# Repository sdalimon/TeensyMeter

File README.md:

# TeensyMeter
A simple voltmeter using a Teensy 3.5/3.6

This was a PCB I made up to experiment with software RMS calculation.

The hardware provides the following:
  - Socket for a Teensy 3.5 or Teensy 3.6 processor board
  - Socket for a SparkFun 7 segment display module (I2C connection only)
  - 4 pushbuttons
  - Differential Amplifier connected to input A9 of the Teensy
  
The input is differential, but not isolated.  The input range is +/- 60 V.  No protection against overvoltage is provided except the series resistors.  Do not connect to hazardous voltages.

The software constantly displays either the average (DC, positive only) voltage or the calculated voltage.  SW1 selects DC and SW2 selects RMS.

Calibration of offset and gain is supported, but the results are pretty good with 0.1% resistors even without calibration.  The calibration constants are stored in the EEPROM and sane defaults are used if the EEPROM is corrupt.  
To calibrate:
  - Connect 0.00 V to the input (short the wires)
  - Press SW3
  - Connect 10.00 V DC to the input
  - Press SW4
  
The hardware was designed in KiCAD 5.1.2.  The deisgn includes both 2 layer and 4 layer layouts.  Only the 2 layer layout is tested.

The software was written using the Arduino SDK with the TeensyDuino add-on.  THe followinjg libraries are used:  Wire, EEPROM, CRC32.

Known issues:
 - The resistor footprints are too small.
 - The UART interface of the 7 segment display would be easier to use.
 - The software should make it harder to accidentally calibrate.

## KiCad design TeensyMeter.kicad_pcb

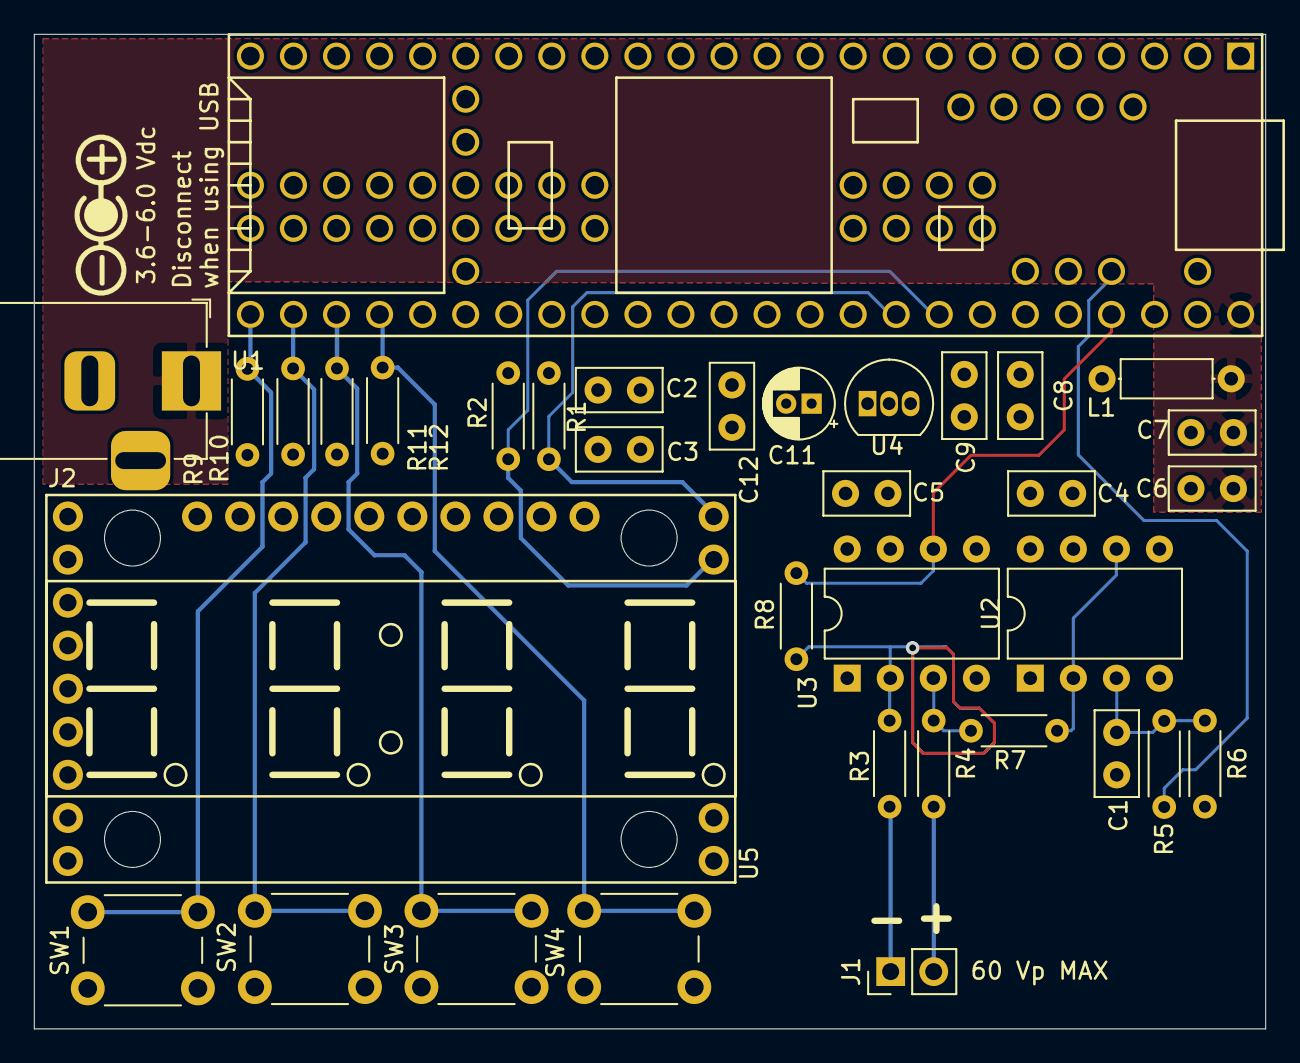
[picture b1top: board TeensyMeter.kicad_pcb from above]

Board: 4 copper layers, 72.6 x 58.7 mm, 35 parts (0 on the bottom side), 20 nets.

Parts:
C1, C3, C4, C5, C7, C9, C12: 100n; C_Disc_D5.0mm_W2.5mm_P2.50mm
C2, C6, C8: 1u; C_Disc_D5.0mm_W2.5mm_P2.50mm
C11: 3u3; CP_Radial_D4.0mm_P1.50mm
J1: Conn_01x02; PinHeader_1x02_P2.54mm_Vertical
J2: Barrel_Jack; BarrelJack_Horizontal
L1: 600; L_Axial_L5.3mm_D2.2mm_P7.62mm_Horizontal_Vishay_IM-1
R1, R2, R5, R6, R9, R10, R11, R12: 10k; R_Axial_DIN0204_L3.6mm_D1.6mm_P5.08mm_Horizontal
R3, R4: 10MEG; R_Axial_DIN0204_L3.6mm_D1.6mm_P5.08mm_Horizontal
R7, R8: 221k; R_Axial_DIN0204_L3.6mm_D1.6mm_P5.08mm_Horizontal
SW1, SW2, SW3, SW4: SW_Push; SW_PUSH_6mm_H4.3mm
U1: Teensy3.6; Teensy35_36
U2, U3: MCP6281RT-E_OT DIP; DIP-8_W7.62mm
U4: LP2950-3.3_TO92; TO-92_Inline
U5: SparkFun_7seg

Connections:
+3.3VA: C4.1, C5.1, C11.1, C12.1, U2.7, U3.7, U4.1
+3V3: C2.1, C3.1, R1.1, R2.1, R9.1, R10.1, R11.1, R12.1, U1.15, U1.26, U1.51, U1.75, U5.6, U5.9, U5.10, U5.20
+5V: C6.1, C7.1, J2.1, L1.2, U1.53
+5VA: C8.1, C9.1, L1.1, U4.3
/A9: R8.1, U1.50, U3.6
/AREF: R5.1, U1.55
/INN: J1.1, R3.2
/INP: J1.2, R4.2
/MID: R7.2, U2.2, U2.6
/SCL: R2.2, U1.46, U5.12
/SDA: R1.2, U1.45, U5.13
GND: C2.2, C3.2, C6.2, C7.2, J2.2, SW1.1, SW2.1, SW3.1, SW4.1, U1.1, U1.27, U1.39, U1.61, U1.62, U1.74, U5.7, U5.8, U5.11, U5.21
GNDA: C1.2, C4.2, C5.2, C8.2, C9.2, C11.2, C12.2, R6.2, U1.52, U2.4, U3.4, U4.2
unnamed: C1.1, R5.2, R6.1, U2.3
unnamed: R3.1, R8.2, U3.2
unnamed: R4.1, R7.1, U3.3
unnamed: R9.2, SW1.2, U1.30
unnamed: R10.2, SW2.2, U1.31
unnamed: R11.2, SW3.2, U1.32
unnamed: R12.2, SW4.2, U1.33

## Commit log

2019-07-22 First Upload
